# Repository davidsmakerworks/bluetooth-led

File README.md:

# bluetooth-led
WS281x LED display driver controlled by Bluetooth (UART)

This is a driver for a string of WS281x (i.e., WS2811 or WS2812B) addressable RGB LEDs. It's designed for the PIC16F18325 using the CLC, SPI, and PWM peripherals to output the data stream in hardware. This significantly reduces CPU load. Updates are handled in the ISR at a rate of up to 60 times per second. At F<sub>osc</sub> = 32 Mhz (F<sub>cy</sub> = 8 MHz), the processing of these interrupts should use less than 0.5% of total CPU time.

A KiCad project is also included for a PCB that supports this driver code.

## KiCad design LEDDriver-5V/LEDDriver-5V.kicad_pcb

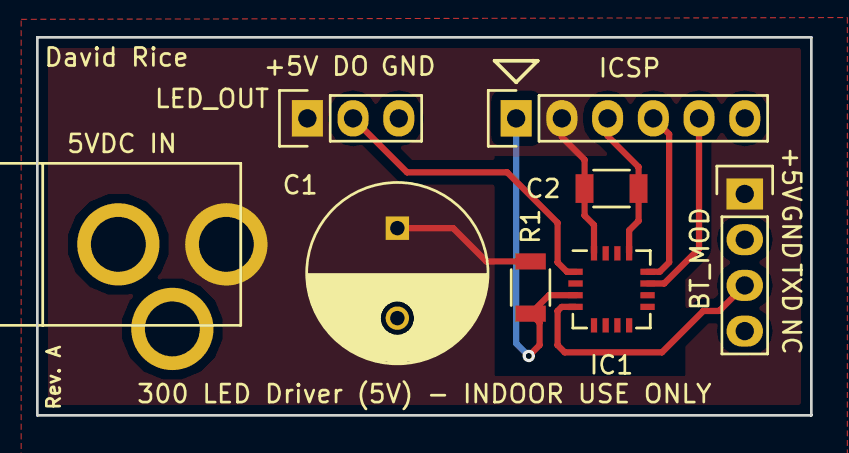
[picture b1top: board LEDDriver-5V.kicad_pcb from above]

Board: 2 copper layers, 43.0 x 21.0 mm, 8 parts (0 on the bottom side), 7 nets.

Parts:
5VDC IN: BARREL_JACK
BT_MOD: BT_MOD; Pin_Header_Straight_1x04
C1: 1000uF; C_Radial_D10_L16_P5
C2: 0.1uf; C_1206
IC1: PIC16F18325-I/JQ; QFN-16-1EP_4x4mm_Pitch0.65mm
ICSP: ICSP; Pin_Header_Straight_1x06
LED_OUT: LED_OUT; Pin_Header_Straight_1x03
R1: 10K; R_1206

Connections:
+5V: 5VDC IN.1, BT_MOD.1, C1.1, C2.1, IC1.16, ICSP.2, LED_OUT.1, R1.2
GND: 5VDC IN.2, 5VDC IN.3, BT_MOD.2, C1.2, C2.2, IC1.13, ICSP.3, LED_OUT.3
unnamed: IC1.1, LED_OUT.2
unnamed: IC1.3, ICSP.1, R1.1
unnamed: BT_MOD.3, IC1.4
unnamed: IC1.11, ICSP.5
unnamed: IC1.12, ICSP.4

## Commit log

2019-06-23 Update folder name
2019-06-24 Update fp-lib-table
2019-12-17 Update DFP
2020-12-07 Remove unnecessary files
